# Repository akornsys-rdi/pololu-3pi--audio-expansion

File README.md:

# Pololu 3PI+ Audio Expansion API

Expansion board to provide audio playback for Pololu 3pi+ 32U4 Robot

## System interconnection diagram

            ┌──────┐   ┌──────┐         D    ┌───┐
            │ USB  │   │ USB  │       ┌──────┤RX │
            │SUBSYS│   │SUBSYS│       │      │ANT│
            ├──────┤   ├──────┤       ▼      └───┘
            ├──────┤ B ├──────┤   ┌──────┐
    ┌───┐   │      │◄──┤      │   │      │   ┌───┐
    │BAT├──►│ 32U4 │   │ SAMD │◄─►┤ TINY ├──►│RGB│
    │LVL│ A │      ├──►│      │ E │      │ D │LED│
    └───┘   ├──────┤ C ├──────┤   └──────┘   └───┘
            ├──────┤   ├──────┤       ▲
            │ROBOT │   │AUDIO │       │      ┌───┐
            │SUBSYS│   │SUBSYS│       └──────┤ID │
            └──────┘   └──────┘         A    │POT│
                                             └───┘
    COMMUNICATION:
    A -> ANALOG             B -> SERIAL DOWNLINK
    C -> SERIAL UPLINK      D -> DIGITAL PROTOCOL
    E -> DIGITAL INTERLINK

## Communication protocols

- Battery reading by analog reading of `A1` of the **ATmega32U4**, the `readBatteryMillivolts()` function (implemented by the Pololu library) provides this functionality.
- Reading the identifier selection potentiometer by analog reading of `A2` from the **ATtiny85**, the `readIdPot()` function (to be implemented in code) provides this functionality.
- Bidirectional communication between **ATmega32U4** and **ATSAMD21** via serial protocol with level shifting at 115200bps. The `Serial1` port is at the **ATmega32U4** end, while the `Serial` port is at the **ATSAMD21** end.
- Reading of the 433MHz radio receiver in 24bit protocol. Realized by the `rc-switch` library (fork).
- WS2812B type RGB LED writing. Realized by the `Adafruit NeoPixel` library.
- Communication primarily one-way from the **ATtiny85** to the **ATSAMD21**. The line level determines what has been received via the radio, leaving the line in high impedance (with pulldown) until the first reception. At startup, different pulses are generated to check the initial status and send the identifier (see corresponding sections).

## Software versions

**ATmega32U4**
- IDE: Arduino IDE 1.8.19
- Board: [Pololu A-Star Boards](https://github.com/pololu/a-star) 4.0.2 by Pololu
- Libraries: 
  + [Pololu3piPlus32U4](https://github.com/pololu/pololu-3pi-plus-32u4-arduino-library) 1.1.2 by Pololu
    * [FastGPIO](https://github.com/pololu/fastgpio-arduino) 2.1.0 by Pololu
    * [USBPause](https://github.com/pololu/usb-pause-arduino) 2.0.0 by Pololu
    * [Pushbutton](https://github.com/pololu/pushbutton-arduino) 2.0.0 by Pololu
    * [PololuBuzzer](https://github.com/pololu/pololu-buzzer-arduino) 1.2.0 by Pololu
    * [PololuHD44780](https://github.com/pololu/pololu-hd44780-arduino) 2.0.0 by Pololu
    * [PololuOLED](https://github.com/pololu/pololu-oled) 2.0.0 by Pololu
    * [PololuMenu](https://github.com/pololu/pololu-menu-arduino) 2.0.0 by Pololu
  + [TimerThree](https://playground.arduino.cc/Code/Timer1/) 1.1.0 by Jesse Tane, Jérôme Despatis, Michael Polli, Dan Clemens, Paul Stoffregen
  + [movingAvg](https://github.com/JChristensen/movingAvg) 2.3.1 by Jack Christensen

**ATSAMD21**
- IDE: Arduino IDE 1.8.19
- Board: Arduino SAMD Boards (32-bits ARM Cortex-M0+) 1.8.7 by Arduino
- Libraries:
  + [Arduino Sound](https://www.arduino.cc/en/Reference/ArduinoSound) 0.2.1 by Arduino
  + [SD](https://www.arduino.cc/en/Reference/SD) 1.2.3 by Arduino
  + [SDConfig](https://www.arduino.cc/reference/en/libraries/sdconfig/) 1.1.0 by Claus Mancini

**ATtiny85**
- IDE: Arduino IDE 1.8.19
- Board: [attiny](https://github.com/damellis/attiny) 1.0.2 by David A. Mellis
- Libreries: 
  + [Adafruit NeoPixel](https://github.com/adafruit/Adafruit_NeoPixel) 1.1.8 by Adafruit
  + [rc-switch](https://github.com/luelista/rc-switch/tree/feature-pcint-rebased) 2.6.2 by Mira Weller (fork).
    * [PinChangeInterrupt](https://github.com/NicoHood/PinChangeInterrupt) 1.2.9 by NicoHood
  + [ATtinySerialOut](https://github.com/ArminJo/ATtinySerialOut) 1.1.0 by Armin Joachimsmeyer

## General information

All **ATtiny85**, **ATSAMD21** and **ATmega32U4** firmware must share common values in the `N_ROBOTS` constant with the value of the maximum number of robots running simultaneously.

## Initial check

The **ATSAMD21** shall perform an initial check at startup, where it will check for the existence and correct access to the SD card, as well as that there is at least one valid audio of each required type. Hardware checks may also be performed. If any of these checks are not correct, the **ATSAMD21** will send the command `#` to the **ATmega32U4**, flash the user LED and, if available, attempt to play a special audio to indicate this circumstance. After this it will latch, ceasing to perform any other functionality until a power cycle is performed.

If the check is successful, it will send the `%` command, and will play, if available, an OK check audio. In the case of having the special audio of check ok, the command of this circumstance will be sent at the end of the reproduction of this audio. Once the initial check has been performed, the system will be able to perform the other functionalities explained in this document.

During the initial check at start-up of **ATSAMD21**, it will maintain the interlink line with **ATtiny85** at high level, thus indicating that it is present and that it is in the process of being checked. As soon as the initial check process is finished, this line will be set low and control of it will be given to the identifier assignment routine.

The **ATtiny85** can set a timeout time waiting for this high level signal, which if it does not appear, it will be considered that communication between these two microcontrollers cannot be established.

If the `MAIN.CFG` file is available on the SD card, it will try to read from it new settings, which will replace the default settings.

The **ATmega32U4** can set a timeout time, after which the Audio Expansion board is considered not available or does not respond. The behavior in this scenario is not determined.

## Identifier assignment operation

The assignment of the identifier is performed at system startup, when the potentiometer that selects the identifier is read. This reading by the **ATtiny85** is processed and converted into a range between `0` and `N_ROBOTS - 1`. The resulting `identifier` is transmitted by a variable width pulse to the **ATSAMD21**. Each identifier is assigned a color on the RGB LED by dividing the color spectrum by the constant `N_ROBOTS` and multiplying the hue angle by `identifier`.

For the pulse indicating the assigned identifier, the **ATSAMD21** after having performed its initial check (being successful), will generate a low level pause on the interlink line of 750µs. After this, it will generate a first high level pulse of 50µs, thus indicating to the **ATtiny85** that it is ready to receive. 5µs later, the **ATtiny85** starts a pulse with a length of (360µs/`N_ROBOTS`)*`identifier`. After this pulse it waits another 25µs at low level before giving control of the line to the remote command routine.

During program execution, the **ATtiny85** periodically reads the potentiometer that selects the identifier for changes. If a change is produced, it displays the new color corresponding to the resulting identifier for three seconds. This functionality has priority in the use of the RGB LED. The new identifier does not replace the previous one, and a power cycle is required for the new identifier selected via the potentiometer to be assigned.

In the communication between the **ATmega32U4** and the **ATSAMD21**, the former can ask at any time for the current identifier, by sending an `@`. If the **ATSAMD21** has already received the identifier from the **ATtiny85**, it will send a character between the `A` and the `~`. Otherwise, it will respond with `@`, thus indicating that it is still unknown. If this circumstance occurs, the **ATmega32U4** must keep asking until it gets a valid answer.

## Remote command operation

The remote command operation allows to pause the robots, or to resume running. It is performed through a 433MHz command, and the command received is processed by the **ATtiny85**. This command is relayed to the **ATSAMD21** via the interlink line level. The **ATSAMD21** will send a command to the **ATmega32U4** with each change of this command. At startup, until the first reception, it should be considered to be in a paused state.

The **ATtiny85** microcontroller decodes the keystroke received from the control and considers whether it is a pause or run command. The interlink line will be set to low or high level respectively. The line remains in high impedance state (with pulldown) until the first command is received.

The RGB LED will blink with the color of the identifier if paused, and will remain fixed for five seconds from the moment of activation, before turning off. It will turn back on with each change of command, remaining in the previous state if a keystroke equal to the current command is repeated.

At the moment of a new change detected by the **ATSAMD21**, it will generate a command via serial port to the **ATmega32U4**. A `&` is sent in case of a run resume command, and a `$` in case of pause or standby. The **ATmega32U4** must receive the command. No response is required.

## Audio playback operation

The **ATmega32U4** shall be able to generate audio playback and end of playback command at any time after the initial check. The **ATSAMD21** shall receive the command and act accordingly. There are two playback commands, depending on their type. The `>` command will initiate playback of path audios (type A), which will be repeated indefinitely if it reaches its end. The `!` command will start the playback of collision audios (type B), which will be played only once. The path audios will stop on receipt of the `=` command.

In the event of path audio playback, the **ATSAMD21** shall choose a random audio file among those provided on the SD card of its type, and start the playback. Randomly, between 1 and 5 times, the same path audio shall be played in successive receptions of that command, after which another audio shall be randomly chosen again with the same strategy.

In the event of collision audio playback, the **ATSAMD21** shall choose a random audio file among those provided on the SD card of its type, and start its playback until the file reaches its end.

If a play command is received while an audio file is already playing, this command will be ignored as long as a special audio is not being played, in which case it will be added to the play queue and played when the special audio is finished.

On the path audio playback stop event, the current audio playback will be stopped, as long as it is of this type. This action will do nothing if a file is not playing or if the playback is of another type.

### File format

The WAVE file format must be PCM mono 16bit at 22050Hz, with extension `.wav`. Any other format cannot be played.

### File names

For path and collision audios, only those files that are consecutive from `000` will be considered.

| File name               | Type     | Description                   |
|-------------------------|----------|-------------------------------|
| `A000.WAV` - `A999.WAV` | Required | Interval of path audios       |
| `B000.WAV` - `B999.WAV` | Required | Interval of collision audios  |
| `CHKOK.WAV`             | Special  | Initial check ok indicator    |
| `CHKKO.WAV`             | Special  | Initial check error indicator |
| `LWBAT.WAV`             | Special  | Low battery indicator         |

Special audios are optional.

## Battery readout operation

The battery level must be constantly monitored, in order to stop the robot if the charge drops below the `LOW_BATT` threshold. This monitoring is done by the **ATmega32U4**, which must send a command to the **ATSAMD21** in case the battery voltage drops below this threshold, which is done by sending a `-` only at the time of detection. The current battery comparison is done using the average of the last readings against the threshold.

This event should cause a latching event, and should not be recoverable until power is cycled. The **ATSAMD21** will play a special audio (if available) once to indicate low battery. If an audio is playing at the time the low battery command is received, the special audio will be retained and played after the previous one has finished. This event does not affect the playback of other audios, which must be stopped if explicitly required by the **ATmega32U4**.

## Debugging and LED status indication

The different LEDs located on the different boards of each robot have a meaning that can help to understand the current behavior of the robot, as well as to detect possible failures and their cause.

| LED                                      | Lighting mode                 | Current status                               | Notes                                                                                               |
|------------------------------------------|-------------------------------|----------------------------------------------|-----------------------------------------------------------------------------------------------------|
| Green LED on main board                  | 1Hz blinking                  | Waiting for identifier of **ATSAMD21**       |                                                                                                     |
| Yellow LED on main board                 | Fixed                         | Motion after obstacle detection or timeout   |                                                                                                     |
| Red LED on main board                    | 2Hz blinking                  | Low battery                                  |                                                                                                     |
| Green, yellow and red LEDs on main board | 10Hz blinking                 | Error in initial check                       | All LEDs simultaneously                                                                             |
| Red LED on Audio Expansion board         | Fixed                         | Battery charging                             | With USB connected to Audio Expansion                                                               |
| Red LED on Audio Expansion board         | Off                           | Battery charged                              | With USB connected to Audio Expansion                                                               |
| Orange LED on Audio Expansion board      | 31Hz blinking                 | SD card not found                            | No SD card                                                                                          |
| Orange LED on Audio Expansion board      | 31Hz blinking                 | Audio files not found or not valid           | With SD card                                                                                        |
| Orange LED on Audio Expansion board      | Fixed                         | Playing audio                                |                                                                                                     |
| RGB LED on Audio Expansion board         | Fixed any color               | Identifying color assigned to the robot      | Right at startup                                                                                    |
| RGB LED on Audio Expansion board         | 15Hz white blinking           | Awaiting communication with **ATSAMD21**     | In start-up sequence                                                                                |
| RGB LED on Audio Expansion board         | Fixed pure green              | Successful communication with **ATSAMD21**   | In start-up sequence after white blinking, duration 500ms                                           |
| RGB LED on Audio Expansion board         | Fixed pure red                | Unsuccessful communication with **ATSAMD21** | In start-up sequence after white blinking, duration 500ms                                           |
| RGB LED on Audio Expansion board         | 8Hz robot identifier blinking | Pause mode                                   | After the start-up sequence                                                                         |
| RGB LED on Audio Expansion board         | Fixed robot identifier        | Active mode                                  | After the start-up sequence, duration 5s                                                            |
| RGB LED on Audio Expansion board         | Off                           | Active mode                                  | After the start-up sequence, after being fixed for 5s                                               |
| RGB LED on Audio Expansion board         | Fixed any color               | Identification color selection               | After the start-up sequence, moving the identifier selection potentiometer or up to 3 seconds later |

## Summary of uplink/downlink commands

| Source         | Destination        | Command   | Description                   |
|----------------|----------------|-----------|-----------------------------------|
| **ATSAMD21**   | **ATmega32U4** | `#`       | Initial check error               |
| **ATSAMD21**   | **ATmega32U4** | `%`       | Initial check ok                  |
| **ATmega32U4** | **ATSAMD21**   | `@`       | Identifier request                |
| **ATSAMD21**   | **ATmega32U4** | `@`       | Answer: Unknown identifier        |
| **ATSAMD21**   | **ATmega32U4** | `A` - `~` | Answer: Identifier number         |
| **ATSAMD21**   | **ATmega32U4** | `$`       | Set pause mode                    |
| **ATSAMD21**   | **ATmega32U4** | `&`       | Set active mode                   |
| **ATmega32U4** | **ATSAMD21**   | `>`       | Start of path audio playback      |
| **ATmega32U4** | **ATSAMD21**   | `=`       | Stop audio path playback          |
| **ATmega32U4** | **ATSAMD21**   | `!`       | Start of collision audio playback |
| **ATmega32U4** | **ATSAMD21**   | `-`       | Low battery indicator             |

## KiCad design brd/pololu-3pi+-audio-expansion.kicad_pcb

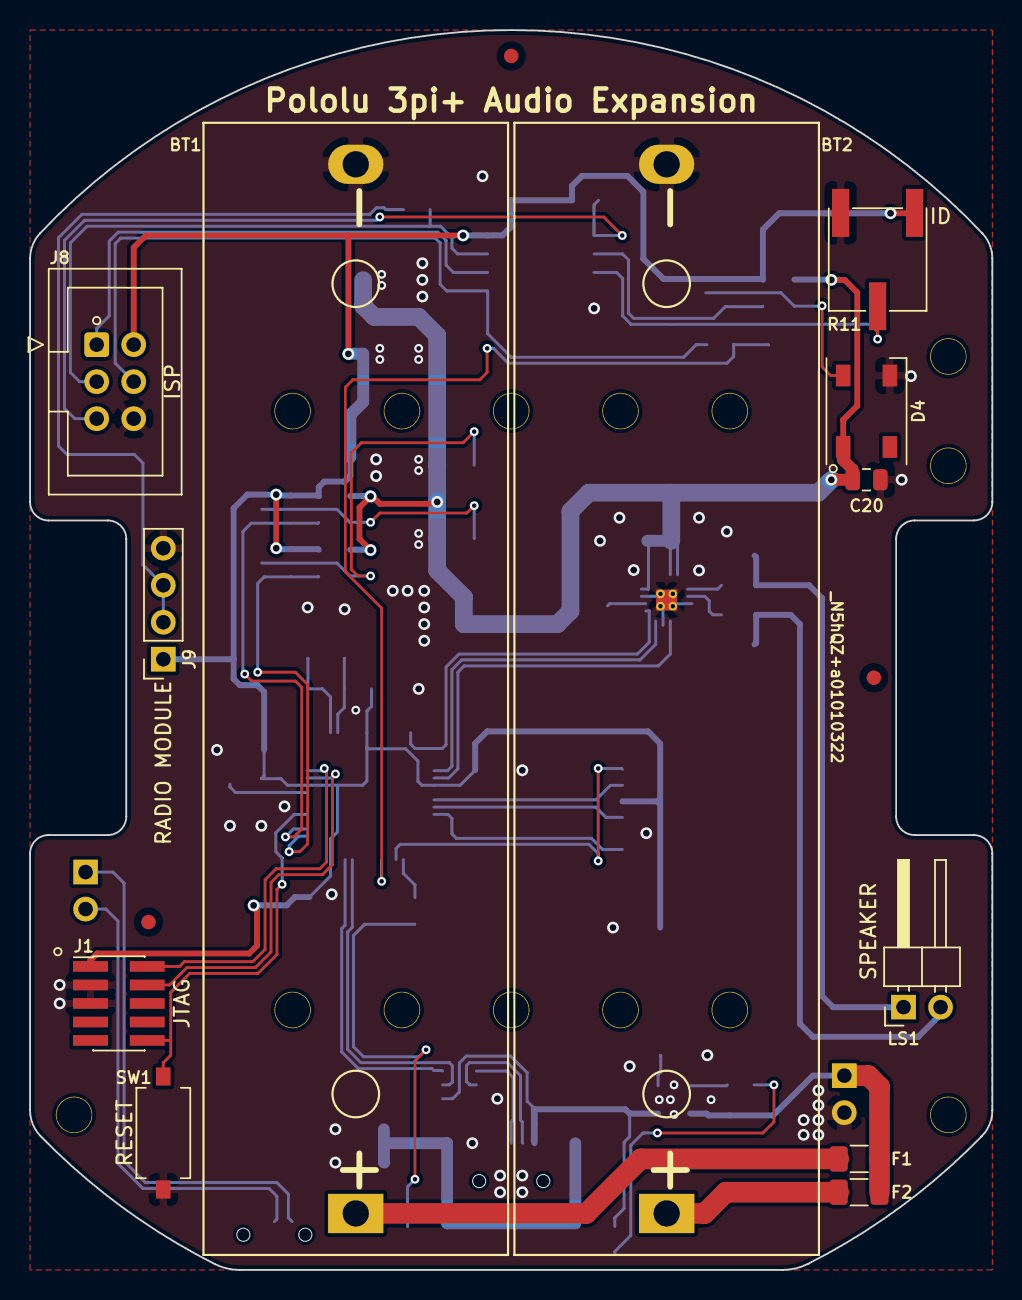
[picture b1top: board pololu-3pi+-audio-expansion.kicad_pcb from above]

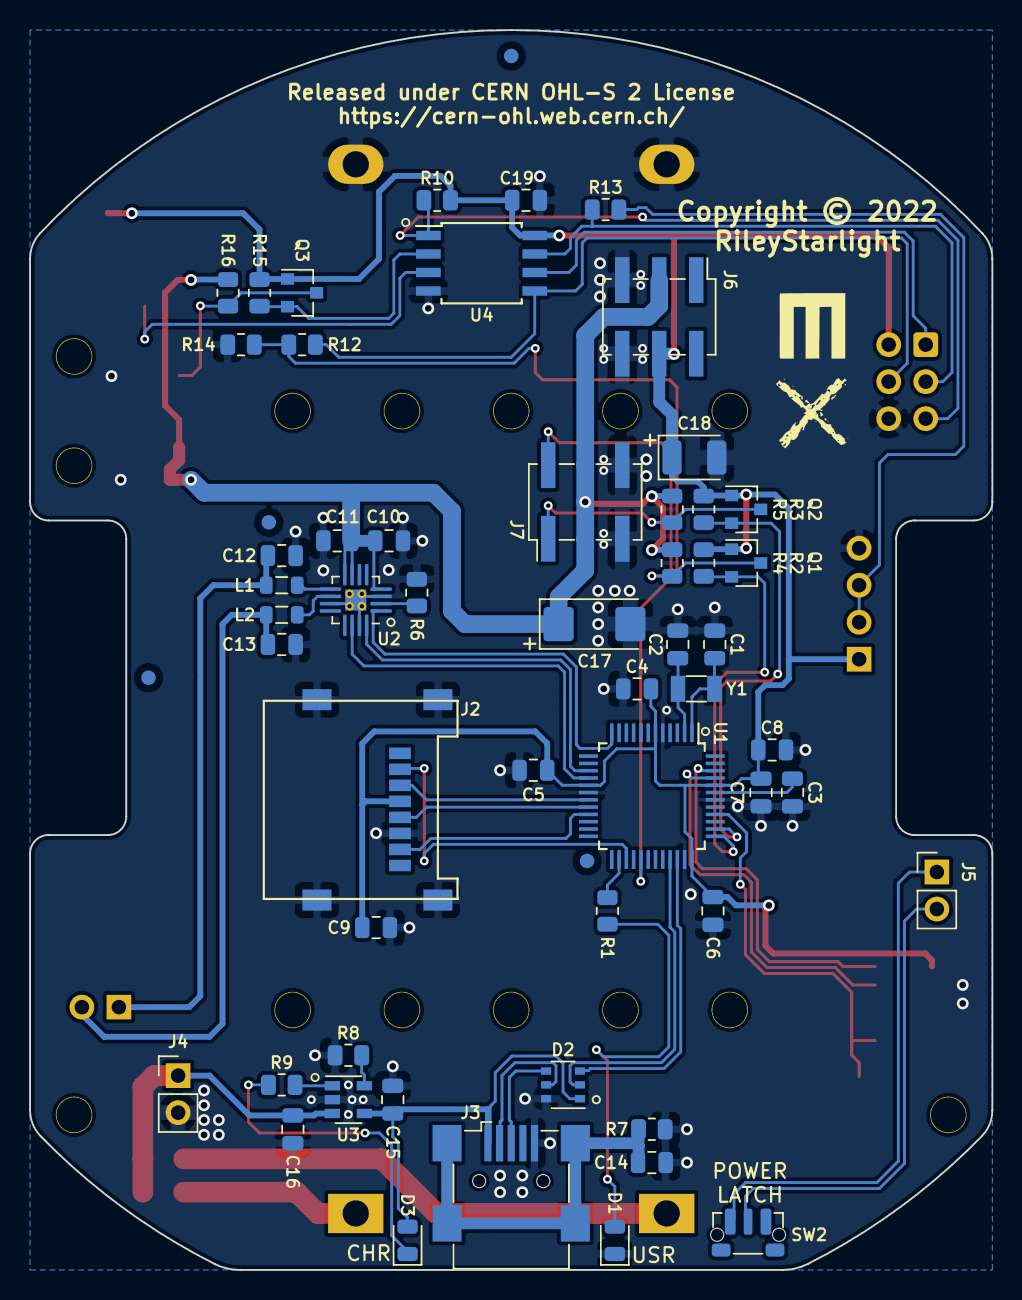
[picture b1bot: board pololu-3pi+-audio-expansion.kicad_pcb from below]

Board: 2 copper layers, 66.0 x 85.1 mm, 66 parts (54 on the bottom side), 50 nets.

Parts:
BT1, BT2: 18650; 18650-holder
C1, C2: 22pF; C_0805_2012Metric
C3: 1µF; C_0805_2012Metric
C4, C5, C6, C7, C9, C10, C19: 100nF; C_0805_2012Metric
C8, C11, C15, C16, C20: 10µF; C_0805_2012Metric
C12, C13: 220pF; C_0805_2012Metric
C14: 4.7nF; C_0805_2012Metric
C17: 150µF; CP_EIA-6032-20_AVX-F
C18: 47µF; CP_EIA-3528-15_AVX-H
D1: ORANGE; LED_0805_2012Metric
D2: STF202; TSOP-6_1.65x3.05mm_P0.95mm
D3: RED; LED_0805_2012Metric
D4: WS2812B; LED_WS2812B_PLCC4_5.0x5.0mm_P3.2mm
F1, F2: 750mA; Fuse_1206_3216Metric
J1: JTAG; PinHeader_2x05_P1.27mm_Vertical_SMD
J2: Micro_SD_Card; 5009010801
J3: USB_B_Mini; USB_Mini-B_Wuerth_65100516121_Horizontal
J4: VBAT; PinHeader_1x02_P2.54mm_Vertical
J5: SWITCH; PinHeader_1x02_P2.54mm_Vertical
J6: POWER; PinHeader_2x03_P2.54mm_Vertical_SMD
J7: EXP; PinHeader_2x03_P2.54mm_Vertical_SMD
J8: ISP; IDC-Header_2x03_P2.54mm_Vertical
J9: RX_MODULE; PinSocket_1x04_P2.54mm_Vertical
L1, L2: Choke; L_0805_2012Metric
LS1: Speaker; PinHeader_1x02_P2.54mm_Horizontal
Q1, Q2, Q3: 2N7002; SOT-23
R1: 220R; R_0805_2012Metric
R2, R3, R4, R5, R10, R15, R16: 10k; R_0805_2012Metric
R6, R14: 100k; R_0805_2012Metric
R7: 1M; R_0805_2012Metric
R8: 2k; R_0805_2012Metric
R9, R12, R13: 1k; R_0805_2012Metric
R11: 10k; Potentiometer_Bourns_3269W_Vertical
SW1: RESET; SW_SPST_EVQPE1
SW2: LATCH; SW_Push_1P1T-MP_NO_Horizontal_Alps_SKRTLAE010
U1: ATSAMD21; TQFP-48_7x7mm_P0.5mm
U2: MAX98357; QFN-16-1EP_3x3mm_P0.5mm_EP1.45x1.45mm_ThermalVias
U3: MCP73831; SOT-23-5
U4: ATtiny85-20SU; SOIJ-8_5.3x5.3mm_P1.27mm
Y1: 32.768kHz; Crystal_SMD_3215-2Pin_3.2x1.5mm

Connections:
+3V3: C4.1, C5.1, C6.1, C7.1, C8.1, C9.1, C18.1, C19.1, J1.1, J2.4, J6.4, J8.2, J9.1, Q1.1, Q2.1, Q3.1, R2.1, R3.1, R10.1, R11.1, R15.1, U1.6, U1.17, U1.36, U1.44, U4.8
+5V: C10.1, C11.1, C17.1, C20.1, D4.1, J6.3, J7.3, J7.4, R4.1, R5.1, R16.1, U2.4, U2.7, U2.8
/Coprocessor/MISO: J8.1, U4.6
/Coprocessor/MOSI: J8.4, R12.2, U4.5
/Coprocessor/SCK: J8.3, R13.2, U4.7
/Coprocessor/~RST: J8.5, R10.2, U4.1
/I2S_BC: U1.15, U2.16
/I2S_DA: U1.12, U2.1
/I2S_LRC: U1.16, U2.14
/PWRL: R12.1, R14.1, U1.29
/RXD: J7.1, Q2.3, R5.2
/SD_CS: J2.2, U1.27
/SD_MISO: J2.7, U1.21
/SD_MOSI: J2.3, U1.19
/SD_SCK: J2.5, U1.20
/SWCLK: J1.4, U1.45
/SWDIO: J1.2, U1.46
/TXD: J7.2, Q1.3, R4.2
/USB_DN: D2.2, U1.33
/USB_DP: D2.3, U1.34
GND: BT1.2, BT2.2, C1.2, C2.2, C3.2, C4.2, C5.2, C6.2, C7.2, C8.2, C9.2, C10.2, C11.2, C12.2, C13.2, C14.2, C15.2, C16.2, C17.2, C18.2, C19.2, C20.2, D1.1, D2.6, D4.3, J1.3, J1.5, J2.6, J2.9, J3.5, J4.2, J6.5, J6.6, J7.5, J7.6, J8.6, J9.4, R6.2, R7.2, R8.2, R11.3, R14.2, SW1.1, U1.5, U1.18, U1.35, U1.42, U2.3, U2.11, U2.15, U2.17, U3.2, U4.4
unnamed: BT1.1, F1.1
unnamed: BT2.1, F2.1
unnamed: C1.1, U1.1, Y1.1
unnamed: C2.1, U1.2, Y1.2
unnamed: C3.1, U1.43
unnamed: C12.1, L1.2, LS1.1
unnamed: C13.1, L2.2, LS1.2
unnamed: C14.1, J3.6, R7.1
unnamed: C15.1, D2.1, D3.2, J3.1, U3.4
unnamed: C16.1, F1.2, F2.2, J4.1, U3.3
unnamed: D1.2, R1.1
unnamed: D2.4, J3.3
unnamed: D2.5, J3.2
unnamed: D3.1, R9.1
unnamed: D4.4, Q3.3, R16.2
unnamed: J1.10, SW1.2, U1.40
unnamed: J5.1, SW2.1
unnamed: J5.2, SW2.2
unnamed: J9.2, J9.3, R13.1
unnamed: L1.1, U2.9
unnamed: L2.1, U2.10
unnamed: Q1.2, R2.2, U1.37
unnamed: Q2.2, R3.2, U1.38
unnamed: Q3.2, R15.2, U4.2
unnamed: R1.2, U1.26
unnamed: R6.1, U2.2
unnamed: R8.1, U3.5
unnamed: R9.2, U3.1
unnamed: R11.2, U4.3

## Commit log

2022-03-13 subida inicial de proyecto
2022-03-13 corregida traducción
2022-03-13 Añadida entrada en tabla README

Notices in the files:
brd/pololu-3pi+-audio-expansion.kicad_pcb:
Released under CERN OHL-S 2 License
https://cern-ohl.web.cern.ch
Copyright © 2022
